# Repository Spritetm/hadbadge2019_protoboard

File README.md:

This is the design of a prototyping cart for the badge for the Hackaday Supercon 2019. You
will need Kicad to open this.

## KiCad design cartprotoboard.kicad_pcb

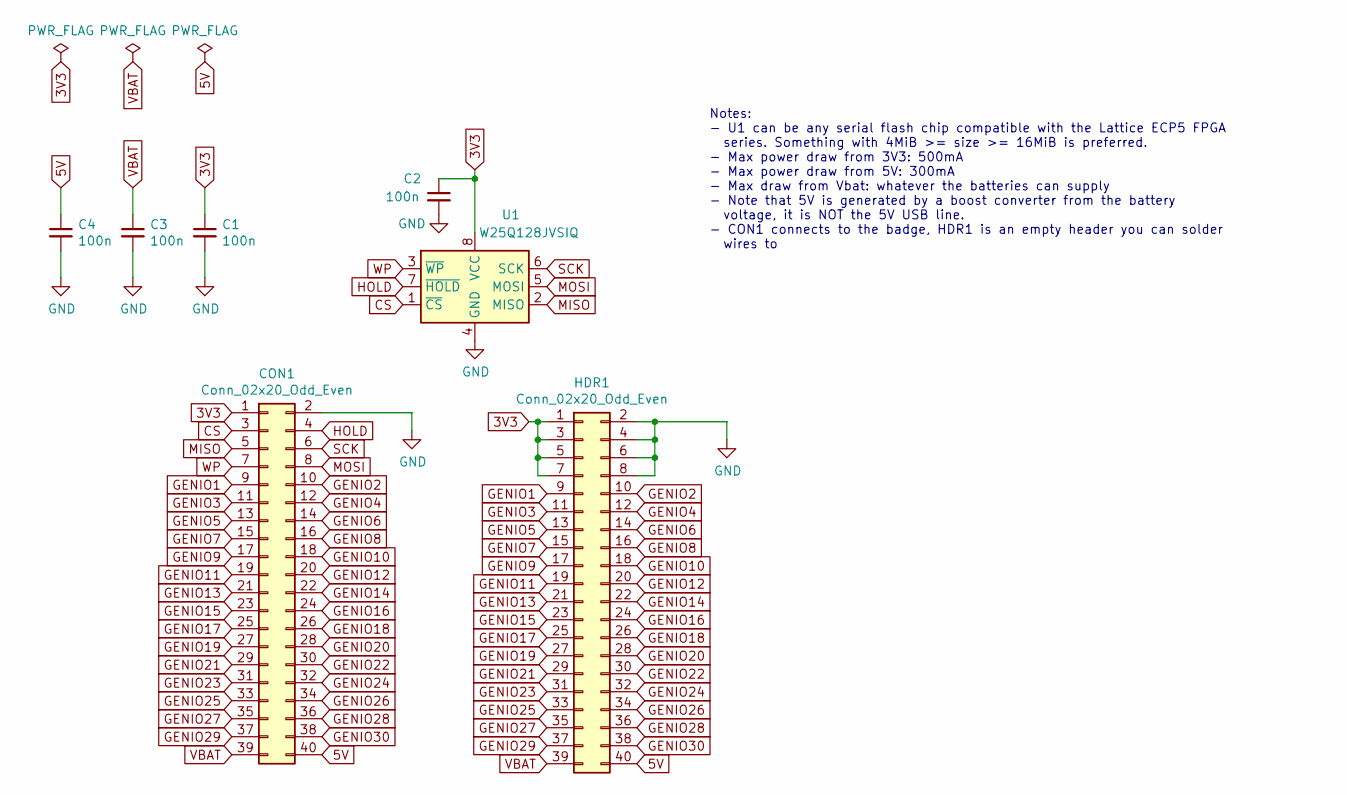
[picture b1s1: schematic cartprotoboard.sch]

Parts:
C1, C2, C3, C4: 100n; C_0603_1608Metric
CON1: Conn_02x20_Odd_Even; PinHeader_2x20_P2.54mm_Horizontal_Mirrored
HDR1: Conn_02x20_Odd_Even; PinHeader_2x20_P2.54mm_Vertical_virt
U1: W25Q128JVSIQ; SSOP-8_5.25x5.24mm_P1.27mm

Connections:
3V3: C1.1, C2.1, CON1.1, HDR1.1, HDR1.3, HDR1.5, HDR1.7, U1.8 (VCC)
5V: C4.1, CON1.40, HDR1.40
CS: CON1.3, U1.1 (~CS)
GENIO1: CON1.9, HDR1.9
GENIO2: CON1.10, HDR1.10
GENIO3: CON1.11, HDR1.11
GENIO4: CON1.12, HDR1.12
GENIO5: CON1.13, HDR1.13
GENIO6: CON1.14, HDR1.14
GENIO7: CON1.15, HDR1.15
GENIO8: CON1.16, HDR1.16
GENIO9: CON1.17, HDR1.17
GENIO10: CON1.18, HDR1.18
GENIO11: CON1.19, HDR1.19
GENIO12: CON1.20, HDR1.20
GENIO13: CON1.21, HDR1.21
GENIO14: CON1.22, HDR1.22
GENIO15: CON1.23, HDR1.23
GENIO16: CON1.24, HDR1.24
GENIO17: CON1.25, HDR1.25
GENIO18: CON1.26, HDR1.26
GENIO19: CON1.27, HDR1.27
GENIO20: CON1.28, HDR1.28
GENIO21: CON1.29, HDR1.29
GENIO22: CON1.30, HDR1.30
GENIO23: CON1.31, HDR1.31
GENIO24: CON1.32, HDR1.32
GENIO25: CON1.33, HDR1.33
GENIO26: CON1.34, HDR1.34
GENIO27: CON1.35, HDR1.35
GENIO28: CON1.36, HDR1.36
GENIO29: CON1.37, HDR1.37
GENIO30: CON1.38, HDR1.38
GND: C1.2, C2.2, C3.2, C4.2, CON1.2, HDR1.2, HDR1.4, HDR1.6, HDR1.8, U1.4 (GND)
HOLD: CON1.4, U1.7 (~HOLD)
MISO: CON1.5, U1.2 (MISO)
MOSI: CON1.8, U1.5 (MOSI)
SCK: CON1.6, U1.6 (SCK)
VBAT: C3.1, CON1.39, HDR1.39
WP: CON1.7, U1.3 (~WP)

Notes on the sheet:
Notes: - U1 can be any serial flash chip compatible with the Lattice ECP5 FPGA series. Something with 4MiB >= size >= 16MiB is preferred. - Max power draw from 3V3: 500mA - Max power draw from 5V: 300mA - Max draw from Vbat: whatever the batteries can supply - Note that 5V is generated by a boost c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

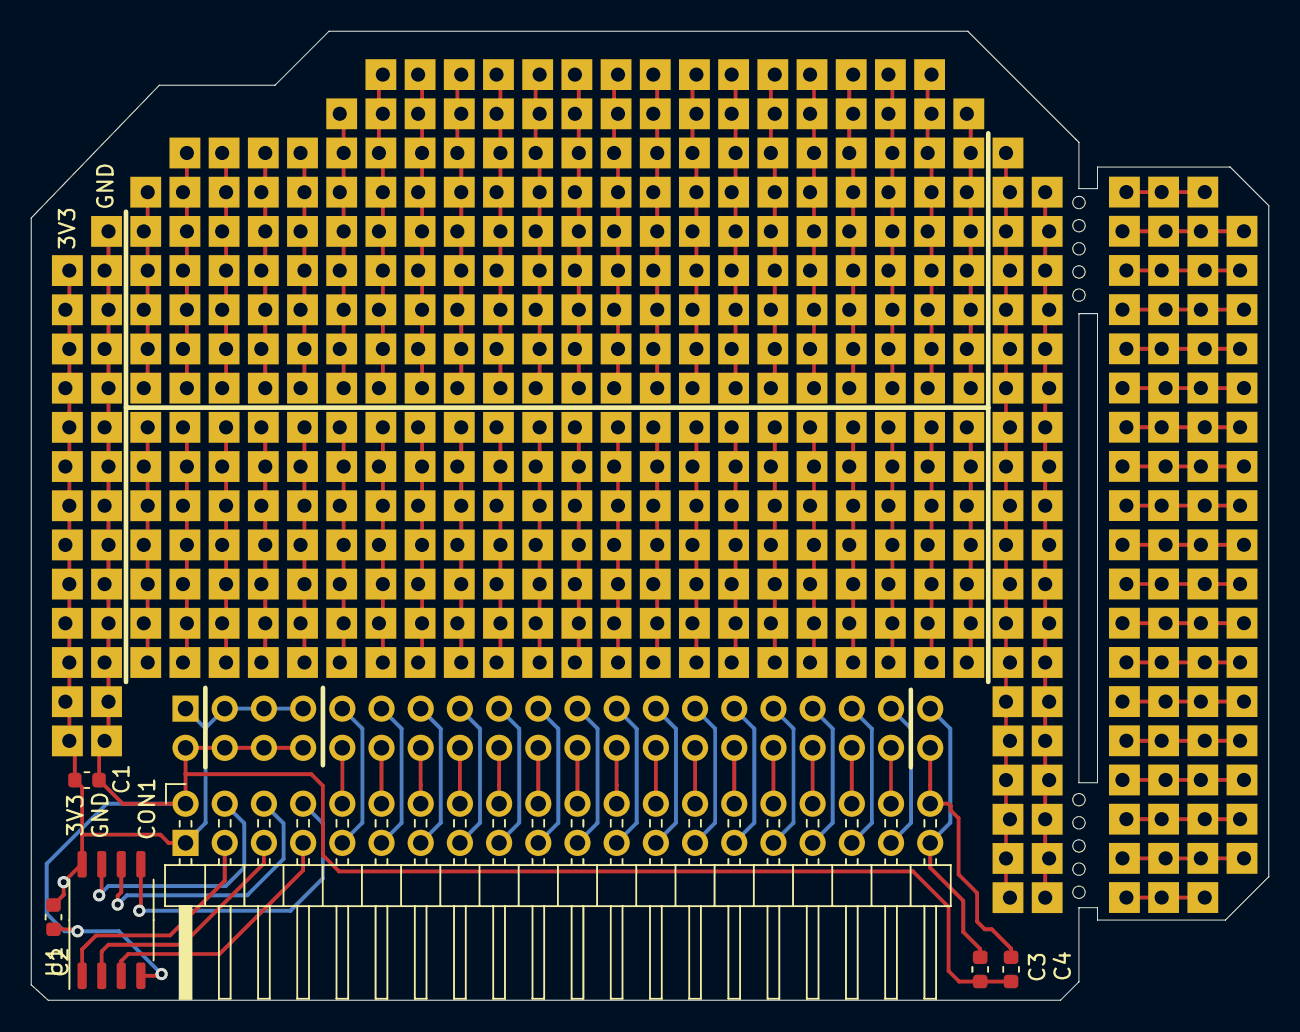
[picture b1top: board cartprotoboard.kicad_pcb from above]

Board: 2 copper layers, 80.2 x 62.8 mm, 7 parts (1 on the bottom side), 40 nets.

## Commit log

2019-10-16 Final board
2019-10-16 Add notes
2019-10-16 Add explanatory text for sidecart
2019-10-16 Add pdfs
2019-10-16 Add readme
2019-11-12 Add mini version and gerbers for both
